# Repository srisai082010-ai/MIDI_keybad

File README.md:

# MIDI_keyboard
his is my custom MIDI keypad PCB designed in KiCad 10. The goal is to build a compact controller for music software using an ESP32-S3-Zero microcontroller, physical switches, capacitive touch keys, and adjustable controls. I designed the schematic and PCB layout as a hands-on electronics project.

## How it is designed to work

- **ESP32-S3-Zero:** The main microcontroller, intended to read inputs and send MIDI messages over USB once firmware is developed.
- **Three Kailh Choc switches (SW1–SW3):** Physical keys for triggering MIDI actions.
- **Seven capacitive touch pads:** Custom copper electrodes that provide additional touch inputs.
- **Rotary encoder (SW5):** A turning control with a push-button function.
- **Two slide potentiometers (RV1 and RV2):** Intended for continuously adjustable MIDI controls.
- **Three RGB LEDs (D1–D3):** Planned visual feedback, placed on the back of the PCB.
 This is my fiishend screenshot of the board:

This is my schematic editor for all of the stuff:

This is .pcb editor screenshot for all the stuff:

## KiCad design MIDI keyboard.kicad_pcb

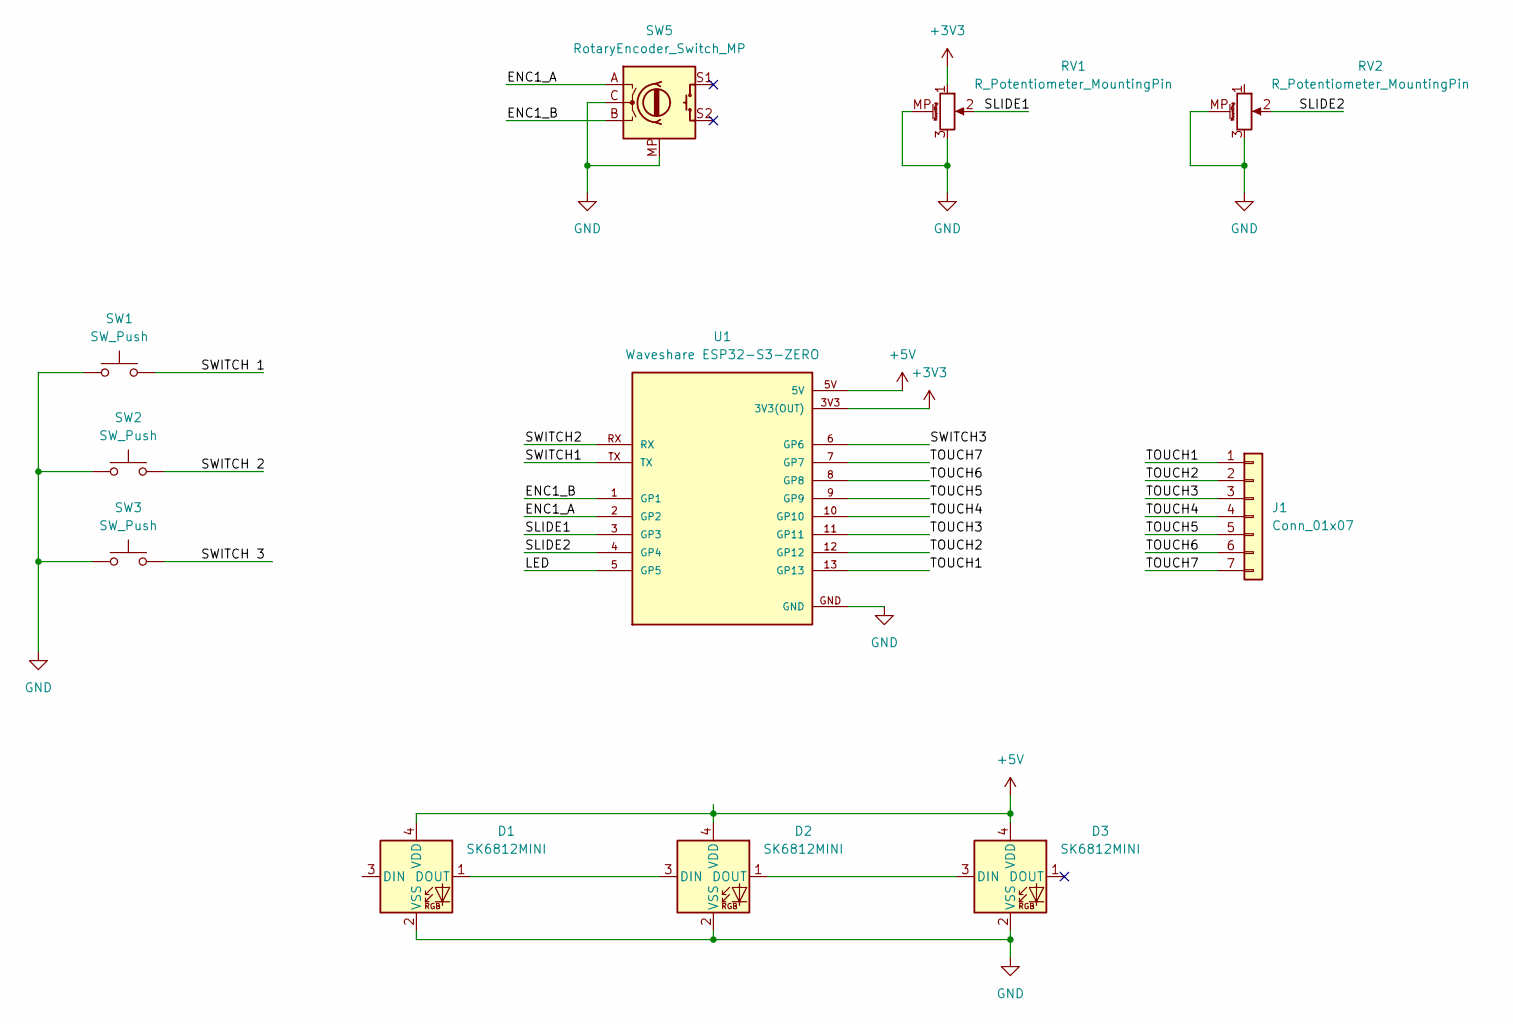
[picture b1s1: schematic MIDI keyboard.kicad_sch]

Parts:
D1, D2, D3: SK6812MINI; LED_SK6812MINI_PLCC4_3.5x3.5mm_P1.75mm
J1: Conn_01x07; keys
RV1, RV2: R_Potentiometer_MountingPin; Potentiometer_Bourns_PTA1543_Single_Slide
SW1, SW2, SW3: SW_Push; Kailh Choc Low-Profile Switches
SW5: RotaryEncoder_Switch_MP; RotaryEncoder_Alps_EC11E-Switch_Vertical_H20mm
U1: Waveshare ESP32-S3-ZERO; Waveshare ESP32-S3-Zero; PARTREV NA

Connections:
+3V3: RV1.1, U1.3V3 (3V3(OUT))
+5V: D1.4 (VDD), D2.4 (VDD), D3.4 (VDD), U1.5V
/<NO NET>: SW5.A, SW5.B, U1.1 (GP1), U1.2 (GP2)
/LED: U1.5 (GP5)
/SLIDE1: RV1.2, U1.3 (GP3)
/SLIDE2: RV2.2, U1.4 (GP4)
/SWITCH1: U1.TX
/SWITCH2: U1.RX
/SWITCH3: U1.6 (GP6)
/SWITCH 1: SW1.2
/SWITCH 2: SW2.2
/SWITCH 3: SW3.2
/TOUCH1: J1.1, U1.13 (GP13)
/TOUCH2: J1.2, U1.12 (GP12)
/TOUCH3: J1.3, U1.11 (GP11)
/TOUCH4: J1.4, U1.10 (GP10)
/TOUCH5: J1.5, U1.9 (GP9)
/TOUCH6: J1.6, U1.8 (GP8)
/TOUCH7: J1.7, U1.7 (GP7)
GND: D1.2 (VSS), D2.2 (VSS), D3.2 (VSS), RV1.3, RV1.MP (MountPin), RV2.3, RV2.MP (MountPin), SW1.1, SW2.1, SW3.1, SW5.C, SW5.MP, U1.GND
unnamed: D1.1 (DOUT), D2.3 (DIN)
unnamed: D2.1 (DOUT), D3.3 (DIN)

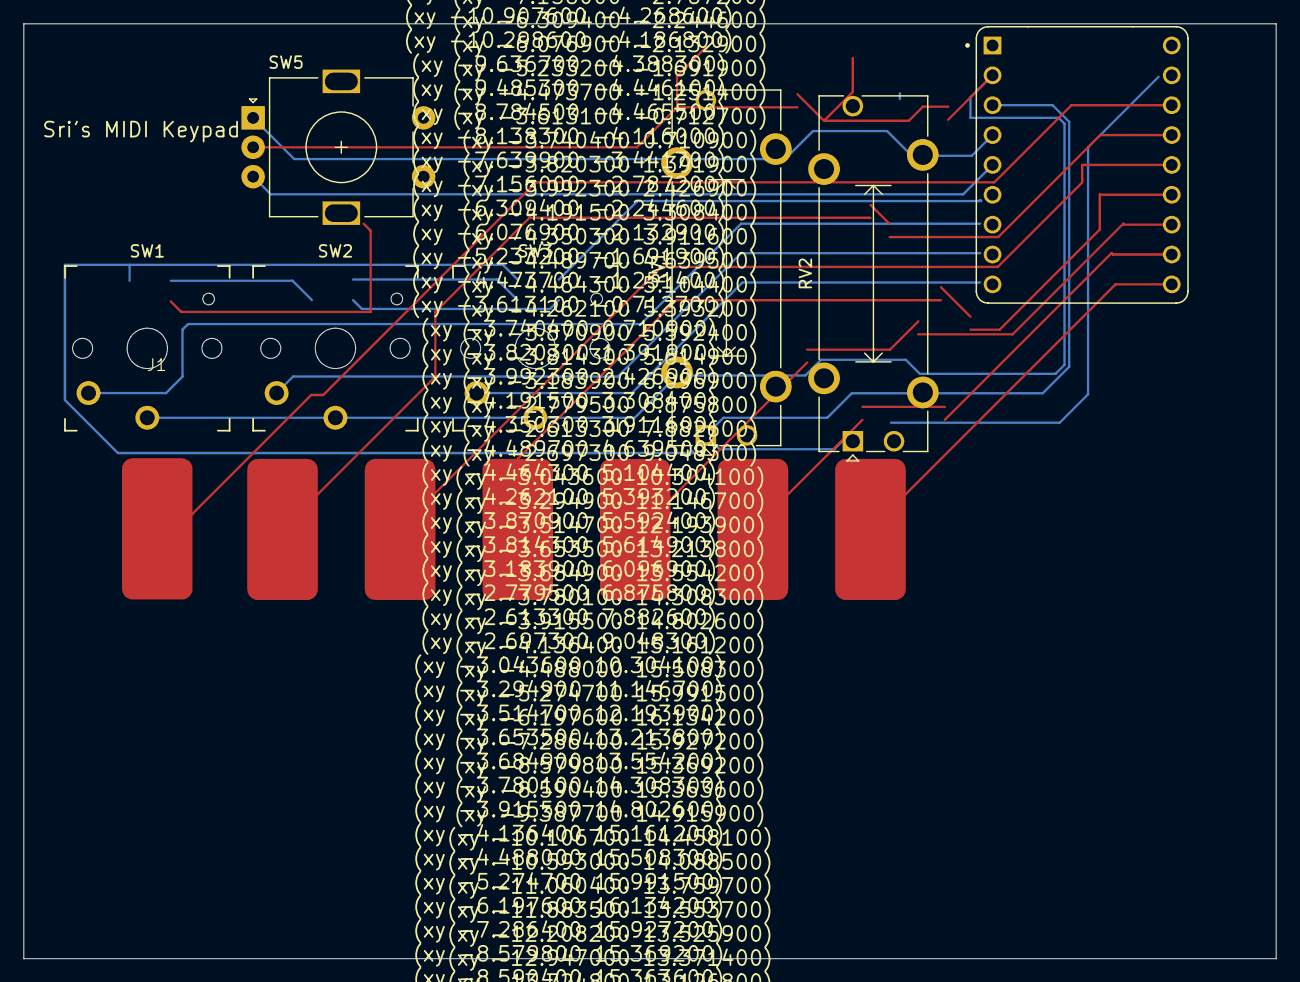
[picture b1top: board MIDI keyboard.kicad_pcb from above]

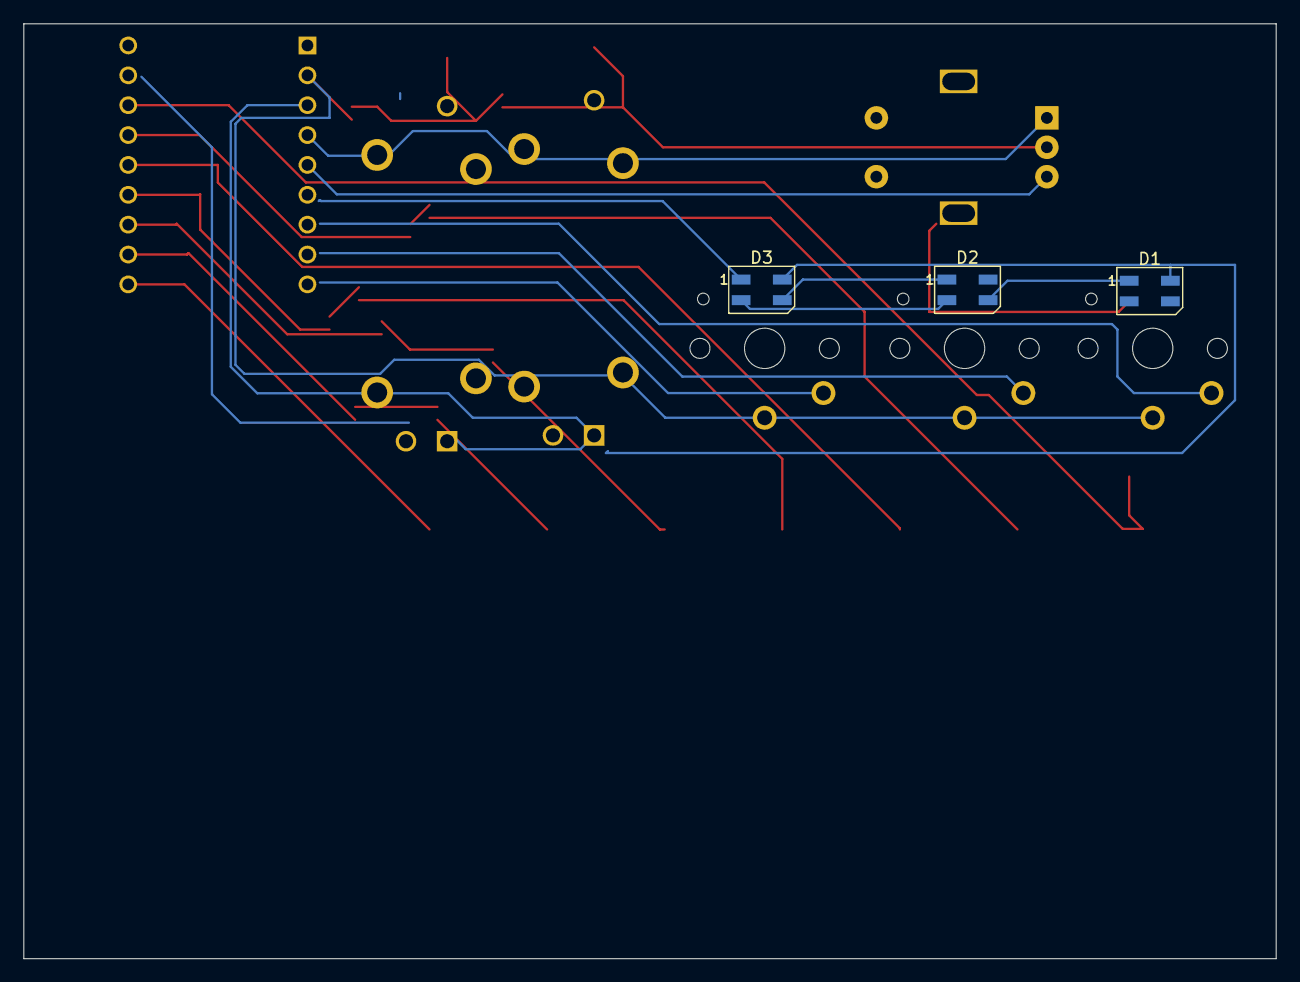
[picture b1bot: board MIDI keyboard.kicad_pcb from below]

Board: 2 copper layers, 106.5 x 79.5 mm, 11 parts (3 on the bottom side), 15 nets.
